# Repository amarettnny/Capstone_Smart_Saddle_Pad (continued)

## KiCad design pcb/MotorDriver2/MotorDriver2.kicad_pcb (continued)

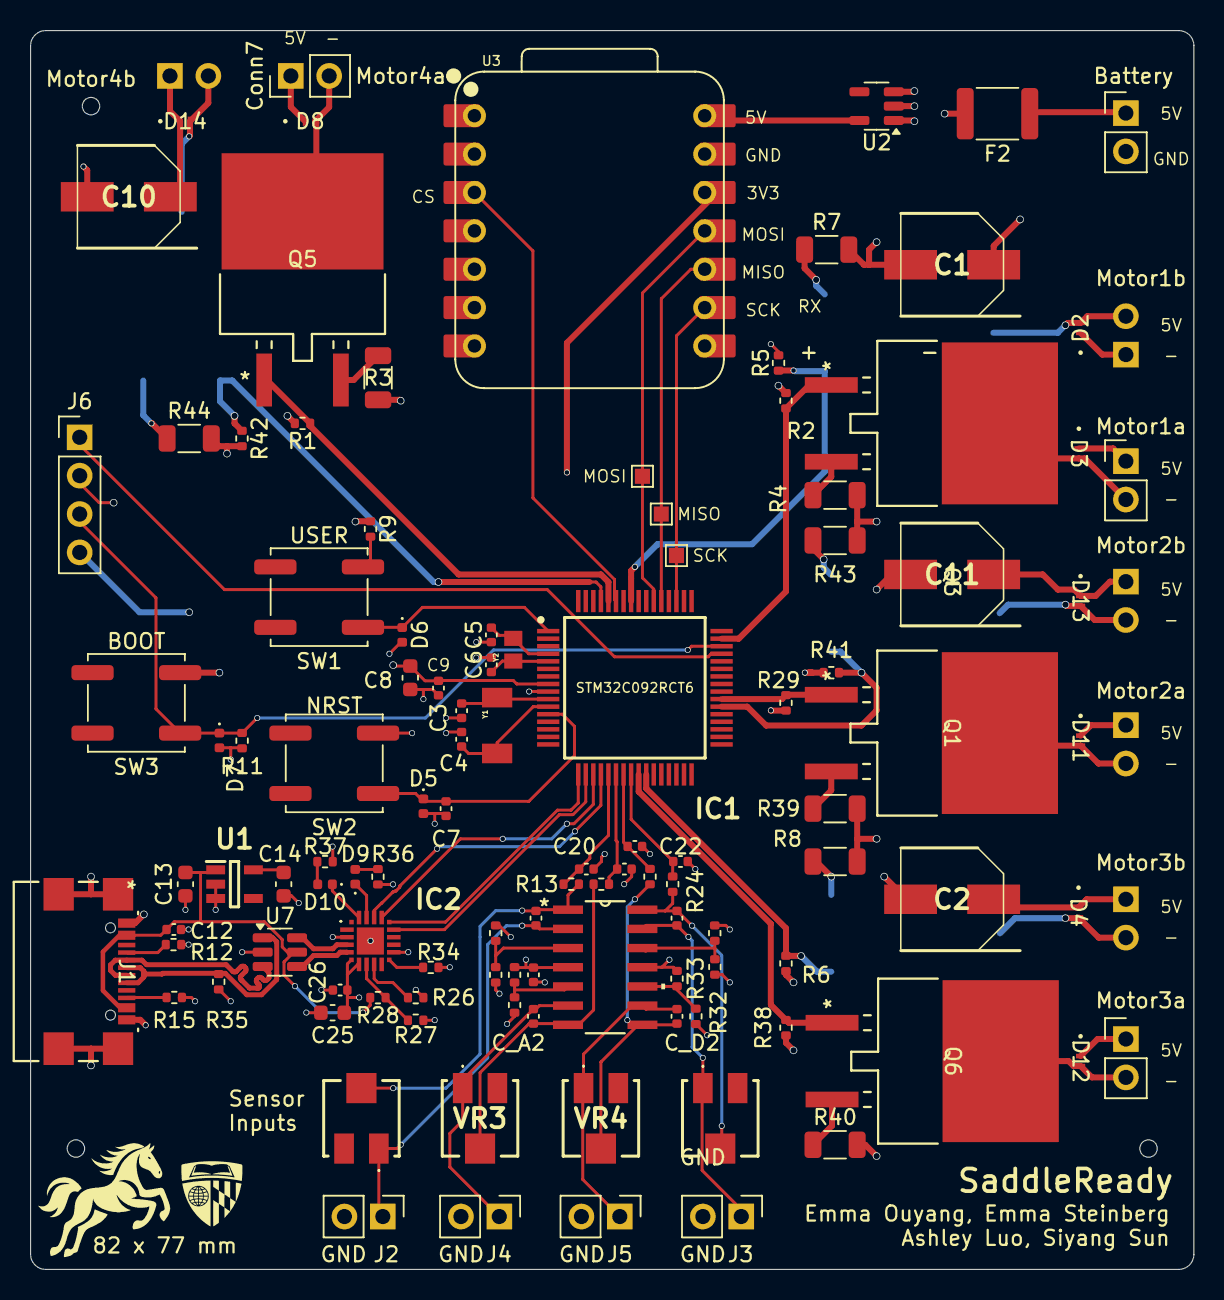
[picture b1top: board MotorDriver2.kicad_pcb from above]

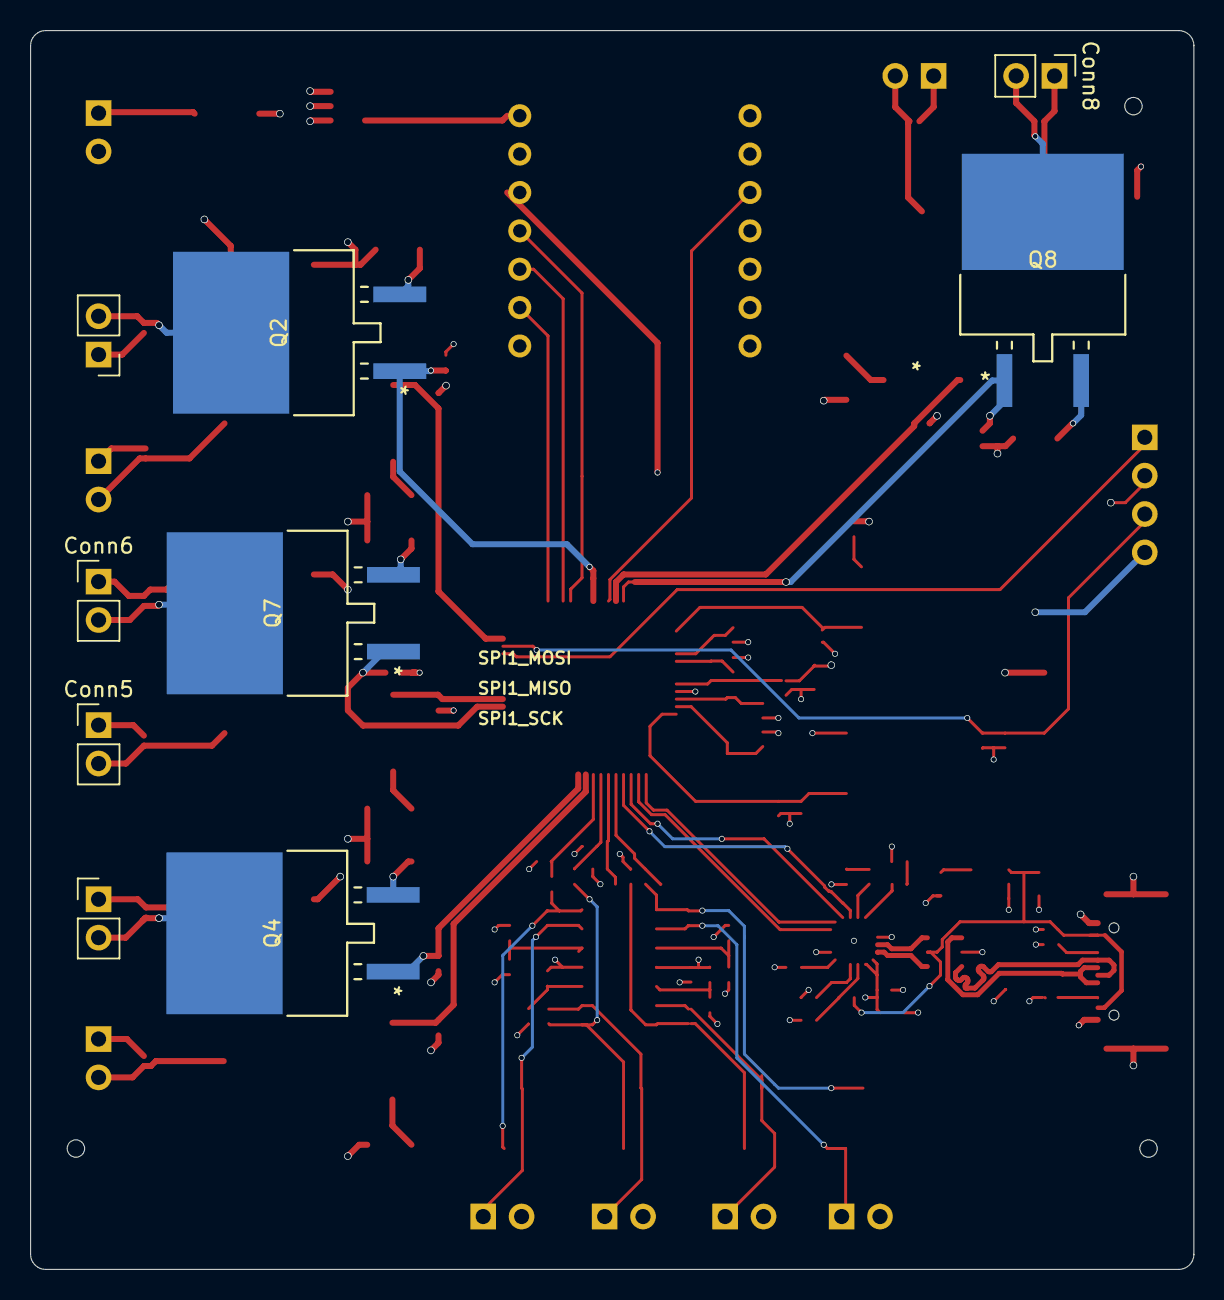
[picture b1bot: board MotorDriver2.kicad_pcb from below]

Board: 4 copper layers, 77.0 x 82.0 mm, 123 parts (9 on the bottom side), 75 nets.

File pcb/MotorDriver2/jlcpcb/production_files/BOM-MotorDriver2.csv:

Comment,Designator,Footprint,LCSC,Quantity
1,"R3,R39,R4,R40,R43,R44,R7,R8",R_1206_3216Metric,C17928,8
1 uF,"C13,C14",C_0603_1608Metric,C15849,2
"1.5k, 1%",R35,R_0402_1005Metric,C25867,1
1.8k,"R18,R19,R31,R33",R_0402_1005Metric,C25871,4
100 nF,"C17,C20,C21,C22,C23,C26,C7,C9",C_0402_1005Metric,C1525,8
100 pF,C12,C_0402_1005Metric,C1546,1
10k,"R1,R11,R16,R17,R2,R29,R30,R32,R34,R38,R41,R42,R5,R6,R9",R_0402_1005Metric,C25744,15
1k,"R26,R36,R37",R_0402_1005Metric,C11702,3
20k,"R13,R14,R24,R25",R_0402_1005Metric,C25765,4
4.7 uF,"C25,C8",C_0603_1608Metric,C19666,2
47 nF,"C_A1,C_A2,C_D1,C_D2",C_0402_1005Metric,C77012,4
"5.1k,10%","R12,R15",R_0402_1005Metric,C25905,2
"7.5 pF, 0.1%","C5,C6",C_0402_1005Metric,C161334,2
"8 pF, 0.1%","C3,C4",C_0402_1005Metric,C3849295,2
CP2102N-A02-GQFN20R,IC2,CP2102NA02GQFN20,C969913,1
ESDALC6V1-1M2,"D5,D6,D7",D_0402_1005Metric,C2649894,3
Honor Elec RVT1H470M0607,"C1,C10,C11,C2",CAPAE680X800N,C3349,4
IRLZ44NSTRLPBF,"Q1,Q2,Q3,Q4,Q5,Q6,Q7,Q8",NMOSGDS_D2PAK_INF,C538199,8
LED,D9,D_0402_1005Metric,C71911,1
LED,D10,D_0402_1005Metric,C74338,1
MAX40200AUK,U2,SOT-23-5,C2649430,1
MINISMDC260F/16-2,F2,Fuse_1812_4532Metric,C16490,1
NCP361SNT1G,U1,SOT95P275X110-5N,C233714,1
SM5819L2-TP,"D11,D12,D13,D14,D2,D3,D4,D8",SDO_SM5819L2-TP_MCE,C6297199,8
STM32C092RCT6,IC1,QFP50P1200X1200X160-64N,C45066876,1
USBLC6-2SC6,U7,SOT-23-6,C7519,1
K2-6639SP-C4SC-04,SW2,K2-6639SP-C4SC-04,,1
Motor2,Conn2,PinHeader_1x02_P2.54mm_Vertical,,1
K2-6639SP-C4SC-04,SW3,K2-6639SP-C4SC-04,,1
Conn_01x02,J2,PinHeader_1x02_P2.54mm_Vertical,,1
32.768 kHz,Y2,MU00527-32.768K,,1
GND,VBAT1,PinHeader_1x02_P2.54mm_Vertical,,1
XIAO-ESP32-C5-DIP,U3,XIAO-ESP32-C5-DIP,,1
48 MHz,Y1,ECS-480-8-30-JGN-TR,,1
Motor4,Conn4,PinHeader_1x02_P2.54mm_Vertical,,1
TS53YJ105MR10,VR2,TS53YJ105MR10,,1
K2-6639SP-C4SC-04,SW1,K2-6639SP-C4SC-04,,1
USB4110-GF-A,J1,USB4110-GF-A_GCT,,1
Conn_01x02,J3,PinHeader_1x02_P2.54mm_Vertical,,1
TS53YJ105MR10,VR1,TS53YJ105MR10,,1
Motor3,Conn3,PinHeader_1x02_P2.54mm_Vertical,,1
Motor1,Conn1,PinHeader_1x02_P2.54mm_Vertical,,1
22.1k,R28,R_0402_1005Metric,,1
TestPoint,TP3,TestPoint_Pad_1.0x1.0mm,,1
TestPoint,TP2,TestPoint_Pad_1.0x1.0mm,,1
TestPoint,TP1,TestPoint_Pad_1.0x1.0mm,,1
Motor8,Conn8,PinHeader_1x02_P2.54mm_Vertical,,1
Motor5,Conn5,PinHeader_1x02_P2.54mm_Vertical,,1
Motor6,Conn6,PinHeader_1x02_P2.54mm_Vertical,,1
Motor7,Conn7,PinHeader_1x02_P2.54mm_Vertical,,1
47.5k,R27,R_0402_1005Metric,,1
LM324DR,U6,D14,,1
Conn_01x02,J4,PinHeader_1x02_P2.54mm_Vertical,,1
Conn_01x02,J5,PinHeader_1x02_P2.54mm_Vertical,,1
TS53YJ105MR10,VR4,TS53YJ105MR10,,1
TS53YJ105MR10,VR3,TS53YJ105MR10,,1
Conn_01x04,J6,PinHeader_1x04_P2.54mm_Vertical,,1

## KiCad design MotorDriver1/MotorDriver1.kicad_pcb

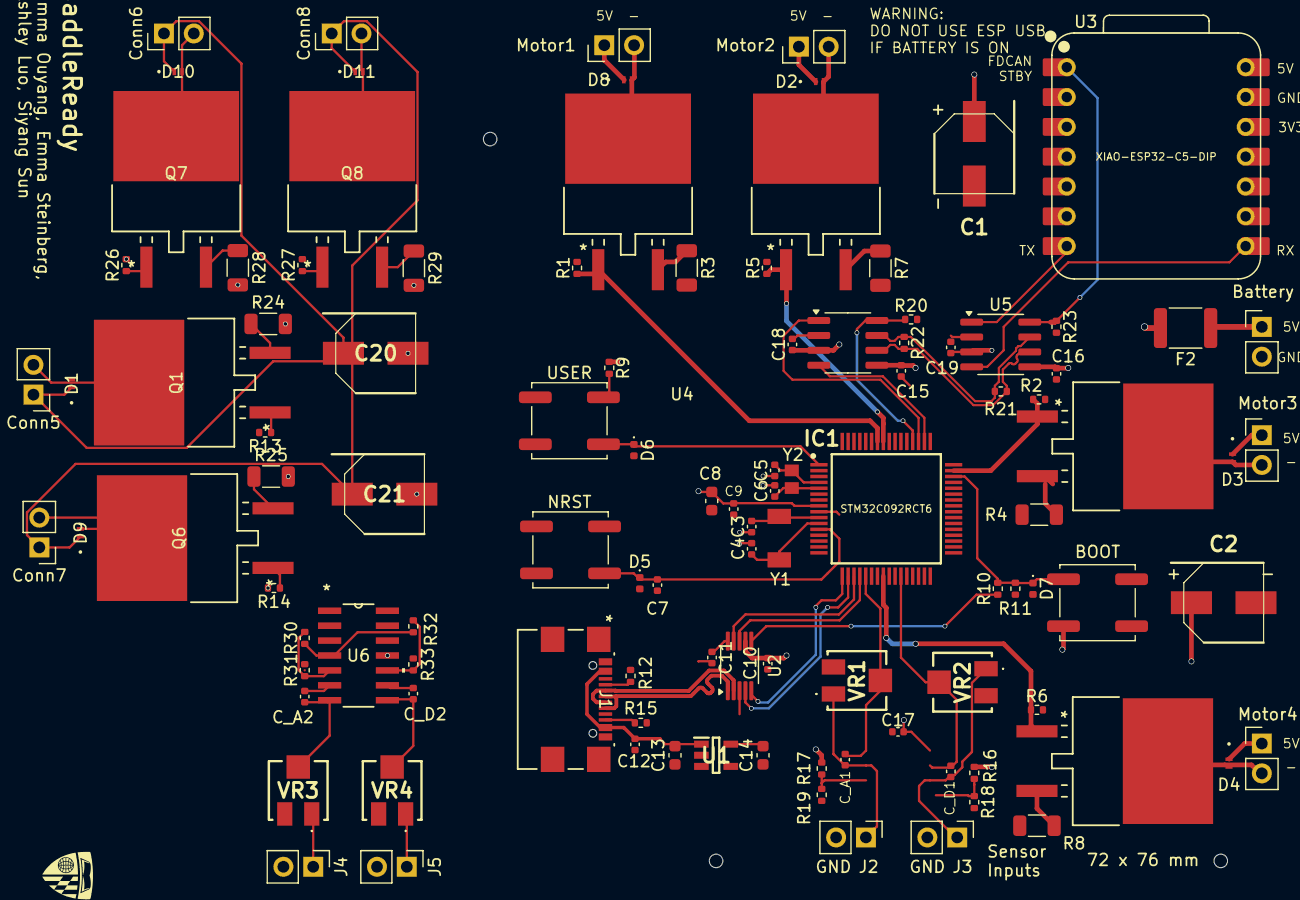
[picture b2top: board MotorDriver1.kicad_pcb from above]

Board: 4 copper layers, 111 parts (0 on the bottom side), 64 nets.

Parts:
C1, C2, C20, C21: MAL214297108E3; CAPAE680X800N
C3, C4: 8 pF, 0.1%; C_0402_1005Metric
C5, C6: 7.5 pF, 0.1%; C_0402_1005Metric
C7, C9, C10, C12, C15, C16, C17, C18, C19: 100 nF; C_0402_1005Metric
C8: 4.7 uF; C_0603_1608Metric
C11: 10 nF; C_0402_1005Metric
C13, C14: 1 uF; C_0603_1608Metric
C_A1, C_A2: 47 nF; C_0402_1005Metric
C_D1, C_D2: 47 nF; C_0402_1005Metric
Conn1: Motor1; PinHeader_1x02_P2.54mm_Vertical
Conn2: Motor2; PinHeader_1x02_P2.54mm_Vertical
Conn3: Motor3; PinHeader_1x02_P2.54mm_Vertical
Conn4: Motor4; PinHeader_1x02_P2.54mm_Vertical
Conn5: Motor5; PinHeader_1x02_P2.54mm_Vertical
Conn6: Motor6; PinHeader_1x02_P2.54mm_Vertical
Conn7: Motor7; PinHeader_1x02_P2.54mm_Vertical
Conn8: Motor8; PinHeader_1x02_P2.54mm_Vertical
D1, D2, D3, D4, D8, D9, D10, D11: SM5819L2-TP; SDO_SM5819L2-TP_MCE
D5, D6, D7: ESDALC6V1-1M2; D_0402_1005Metric
F2: MINISMDC260F/16-2; Fuse_1812_4532Metric
H1, H2, H3: MountingHole; ToolingHole_1.152mm
IC1: STM32C092RCT6; QFP50P1200X1200X160-64N
J1: GT-USB-7010ASV; USB4110-GF-A_GCT
J2, J3, J4, J5: Conn_01x02; PinHeader_1x02_P2.54mm_Vertical
Q1, Q2, Q3, Q4, Q5, Q6, Q7, Q8: IRLZ44NSTRLPBF; NMOSGDS_D2PAK_INF
R1, R2, R5, R6, R9, R11, R13, R14, R16, R17, R20, R23, R26, R27, R30, R32: 10k; R_0402_1005Metric
R3, R4, R7, R8, R24, R25, R28, R29: 1; R_1206_3216Metric
R10: DNP; R_0402_1005Metric
R12, R15: 5.1k,10%; R_0402_1005Metric
R18, R19, R31, R33: 1.8k; R_0402_1005Metric
R21, R22: 120; R_0402_1005Metric
SW1, SW2, SW3: K2-6639SP-C4SC-04
U1: NCP361SNT1G; SOT95P275X110-5N
U2: CH340X; MSOP-10_3x3mm_P0.5mm
U3: XIAO-ESP32-C5-DIP
U4, U5: MCP2562FDT-H/SN; SOIC-8_3.9x4.9mm_P1.27mm
U6: LM324DR; D14
VBAT1: GND; PinHeader_1x02_P2.54mm_Vertical
VR1, VR2, VR3, VR4: TS53YJ105MR10
Y1: 48 MHz; ECS-480-8-30-JGN-TR
Y2: 32.768 kHz; MU00527-32.768K

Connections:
3V3: C8.2, C9.1, C10.2, C15.1, C16.1, C17.1, IC1.8 (VDD/VDDA), R9.1, R16.1, R17.1, R30.1, R32.1, SW3.2, U2.7 (VCC), U3.12 (3V3), U4.5 (Vio), U5.5 (Vio), U6.4 (VCC)
5V: C1.1 (+), C2.1 (+), C18.1, C19.1, C20.1 (+), C21.1 (+), Conn1.1, Conn2.1, Conn3.1, Conn4.1, Conn5.1, Conn6.1, Conn7.1, Conn8.1, D1.1 (K), D2.1 (K), D3.1 (K), D4.1 (K), D8.1 (K), D9.1 (K), D10.1 (K), D11.1 (K), F2.2, U3.14 (VBUS), U4.3 (VDD), U5.3 (VDD)
5V_USB: C14.2, U1.5 (OUT)
!CTS: IC1.17 (PA0), U2.5 (~CTS)
!DTR: R10.1, U2.6 (TNOW/~DTR)
!RTS: IC1.18 (PA1), U2.4 (~RTS)
/FDCAN/CAN_N: R21.2, R22.2, U4.6 (CANL), U5.6 (CANL)
/FDCAN/CAN_P: R21.1, R22.1, U4.7 (CANH), U5.7 (CANH)
/motorDriver_Pads12/Motor1-: Conn1.2, D8.2 (A), Q5.2 (D)
/motorDriver_Pads12/Motor2-: Conn2.2, D2.2 (A), Q2.2 (D)
/motorDriver_Pads12/Motor3-: Conn3.2, D3.2 (A), Q3.2 (D)
/motorDriver_Pads12/Motor4-: Conn4.2, D4.2 (A), Q4.2 (D)
/motorDriver_Pads34/Motor5-: Conn5.2, D1.2 (A), Q1.2 (D)
/motorDriver_Pads34/Motor6-: Conn6.2, D10.2 (A), Q7.2 (D)
/motorDriver_Pads34/Motor7-: Conn7.2, D9.2 (A), Q6.2 (D)
/motorDriver_Pads34/Motor8-: Conn8.2, D11.2 (A), Q8.2 (D)
/stm32/PC14: C5.2, IC1.4 (PC14-OSCX_IN), Y2.2
/stm32/PC15: C6.1, IC1.5 (PC15-OSCX_OUT), Y2.1
/stm32/PF0: C3.2, IC1.10 (PF0-OSC_IN), Y1.2
/stm32/PF1: C4.1, IC1.11 (PF1-OSC_OUT), Y1.1
BOOT: D7.1 (K), IC1.46 (PA14-BOOT0), R10.2, R11.1, SW3.4
FDCAN_RX_ESP: U3.8 (GPIO20_D7_RX), U5.4 (RXD)
FDCAN_RX_STM: IC1.50 (PD0), U4.4 (RXD)
FDCAN_STBY_ESP: R23.1, U3.1 (GPIO2_A0_D0), U5.8 (STBY)
FDCAN_STBY_STM: IC1.52 (PD2), R20.1, U4.8 (STBY)
FDCAN_TX_ESP: U3.7 (GPIO21_D6_TX), U5.1 (TXD)
FDCAN_TX_STM: IC1.51 (PD1), U4.1 (TXD)
GND: C1.2 (-), C2.2 (-), C3.1, C4.2, C5.1, C6.2, C7.2, C8.1, C9.2, C10.1, C11.2, C12.1, C13.1, C14.1, C15.2, C16.2, C17.2, C18.2, C19.2, C20.2 (-), C21.2 (-), D5.2 (A), D6.2 (A), D7.2 (A), IC1.9 (VSS/VSSA), J1.15 (GND), J1.16 (GND), J1.17 (GND), J1.18 (GND), J1.A1-B12 (GND), J1.A12-B1 (GND), J2.2, J3.2, J4.2, J5.2, R1.2, R2.2, R3.2, R4.2, R5.2, R6.2, R7.2, R8.2, R11.2, R12.1, R13.2, R14.2, R15.1, R18.2, R19.2, R20.2, R23.2, R24.2, R25.2, R26.2, R27.2, R28.2, R29.2, R31.2, R33.2, SW2.2, U1.2 (GND), U1.3 (~EN), U2.3 (GND), U3.13 (GND), U4.2 (VSS), U5.2 (VSS), U6.11 (GND), VBAT1.2
Motor1_PWM: IC1.58 (PB4), Q1.1 (G), Q5.1 (G), R1.1, R13.1
Motor2_PWM: IC1.57 (PB3), Q2.1 (G), Q7.1 (G), R5.1, R26.1
Motor3_PWM: IC1.47 (PA15), Q3.1 (G), Q6.1 (G), R2.1, R14.1
Motor4_PWM: IC1.24 (PA7), Q4.1 (G), Q8.1 (G), R6.1, R27.1
NRST: C7.1, D5.1 (K), IC1.12 (PF2-NRST), SW2.4
unnamed: J1.A5 (CC1), R12.2
unnamed: J1.B5 (CC2), R15.2
unnamed: Q1.3 (S), R24.1
unnamed: Q5.3 (S), R3.1
unnamed: Q2.3 (S), R7.1
unnamed: Q3.3 (S), R4.1
unnamed: Q4.3 (S), R8.1
unnamed: Q6.3 (S), R25.1
unnamed: Q7.3 (S), R28.1
unnamed: Q8.3 (S), R29.1
unnamed: R9.2, SW1.2
unnamed: C11.1, U2.10 (V3)
unnamed: F2.1, VBAT1.1
SensorAIn: C_A1.2, J2.1, U6.2 (1IN-), VR1.A1 (CCW)
SensorAOut: C_A1.1, IC1.21 (PA4), U6.1 (1OUT), VR1.B1 (WIPER)
SensorA_0.5V: R17.2, R19.1, U6.3 (1IN+)
SensorBIn: C_A2.2, J4.1, U6.6 (2IN-), VR3.A1 (CCW)
SensorBOut: C_A2.1, U6.7 (2OUT), VR3.B1 (WIPER)
SensorB_0.5V: R30.2, R31.1, U6.5 (2IN+)
SensorCIn: C_D2.1, J5.1, U6.9 (3IN-), VR4.A1 (CCW)
SensorCOut: C_D2.2, U6.8 (3OUT), VR4.B1 (WIPER)
SensorC_0.5V: R32.2, R33.1, U6.10 (3IN+)
SensorDIn: C_D1.1, J3.1, U6.13 (4IN-), VR2.A1 (CCW)
SensorDOut: C_D1.2, IC1.27 (PB0), U6.14 (4OUT), VR2.B1 (WIPER)
SensorD_0.5V: R16.2, R18.1, U6.12 (4IN+)
USART2_RX: IC1.20 (PA3), U2.8 (TXD)
USART2_TX: IC1.19 (PA2), U2.9 (RXD)
USB_D+: J1.A6 (DP1), J1.B6 (DP2), U2.1 (UD+)
USB_D-: J1.A7 (DN1), J1.B7 (DN2), U2.2 (UD-)
USER_BTN: D6.1 (K), IC1.1 (PC11), SW1.4
VBUS: C12.2, C13.2, J1.A4-B9 (VBUS), J1.A9-B4 (VBUS), U1.1 (IN)

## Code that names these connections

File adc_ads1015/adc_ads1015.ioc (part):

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Mcu.Name=STM32C092RCTx
Mcu.Package=LQFP64
Mcu.UserName=STM32C092RCTx
PA13.GPIOParameters=GPIO_Label
PA13.GPIO_Label=SWDIO
PA13.Signal=DEBUG_SWDIO
PA14-BOOT0.GPIOParameters=GPIO_Label
PA14-BOOT0.GPIO_Label=SWCLK
PA14-BOOT0.Signal=DEBUG_SWCLK
PA2.GPIOParameters=GPIO_Label
PA2.GPIO_Label=VCP_TX
PA2.Mode=Asynchronous
PA2.Signal=USART2_TX
PA3.GPIOParameters=GPIO_Label
PA3.GPIO_Label=VCP_RX
PA3.Mode=Asynchronous
PA3.Signal=USART2_RX
PA5.GPIOParameters=GPIO_Label
PA5.GPIO_Label=User LED1
PA5.Signal=GPIO_Output
PA6.Mode=I2C
PA6.Signal=I2C2_SDA
PA7.Mode=I2C
PA7.Signal=I2C2_SCL
PC13.GPIOParameters=GPIO_Label
PC13.GPIO_Label=User button
PC13.Signal=GPIO_Input
PC14-OSCX_IN(PC14).GPIOParameters=GPIO_Label
PC14-OSCX_IN(PC14).GPIO_Label=OSCX_IN
PC14-OSCX_IN(PC14).Signal=RCC_OSCX_IN
PC15-OSCX_OUT(PC15).GPIOParameters=GPIO_Label
PC15-OSCX_OUT(PC15).GPIO_Label=OSCX_OUT
PC15-OSCX_OUT(PC15).Signal=RCC_OSCX_OUT
PF0-OSC_IN(PF0).GPIOParameters=GPIO_Label
PF0-OSC_IN(PF0).GPIO_Label=OSC_IN
PF0-OSC_IN(PF0).Signal=RCC_OSC_IN
PF1-OSC_OUT(PF1).GPIOParameters=GPIO_Label
PF1-OSC_OUT(PF1).GPIO_Label=OSC_OUT
PF1-OSC_OUT(PF1).Signal=RCC_OSC_OUT
RCC.HSE_VALUE=8000000
RCC.SYSCLKFreq_VALUE=12000000
board=NUCLEO-C092RC
boardIOC=true

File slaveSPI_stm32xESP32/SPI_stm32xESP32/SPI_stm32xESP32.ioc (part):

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Mcu.Name=STM32C092RCTx
Mcu.Package=LQFP64
Mcu.UserName=STM32C092RCTx
PA2.Mode=Asynchronous
PA2.Signal=USART2_TX
PA3.Mode=Asynchronous
PA3.Signal=USART2_RX
PA5.Mode=Full_Duplex_Slave
PA5.Signal=SPI1_SCK
PA6.Mode=Full_Duplex_Slave
PA6.Signal=SPI1_MISO
PA7.Mode=Full_Duplex_Slave
PA7.Signal=SPI1_MOSI
PC13.Signal=GPIO_Input
PD0.Signal=FDCAN1_RX
PD1.Signal=FDCAN1_TX
PF0-OSC_IN(PF0).Mode=HSE-External-Oscillator
PF0-OSC_IN(PF0).Signal=RCC_OSC_IN
PF1-OSC_OUT(PF1).Mode=HSE-External-Oscillator
PF1-OSC_OUT(PF1).Signal=RCC_OSC_OUT
RCC.HSE_VALUE=48000000
RCC.SYSCLKFreq_VALUE=48000000
RCC.SYSCLKSource=RCC_SYSCLKSOURCE_HSE
board=custom

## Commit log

2026-01-29 Created new branch
2026-01-29 Update README.md with ESP-IDF instructions
2026-01-29 Setting up esp-idf (missing .vscode directory
2026-01-29 Finished setting up esp-idf with VSCode
2026-02-05 Wrote initial BLE code
2026-03-02 Latest updates
2026-03-02 Created gitignore file
2026-03-02 Created PCB schematic
2026-03-02 added dummy files to empty footprint and symbol folders
2026-03-02 Set up KiCad libraries & STM32 page
2026-03-03 Edited STM32 schematic
2026-03-03 Added net labels and global lables to motor driver
2026-03-08 added pressure sensor and flags to STM need op amp rails
2026-03-08 added op amp rails
2026-03-08 input output flags for sensor signals
2026-03-09 updated motor and sensor schematics and added footprints
2026-03-12 missing crystal verification
2026-03-12 Updated footprints
2026-03-12 assigned eo footprints
2026-03-12 laid out PCB
2026-03-12 modifications to PCB layout
2026-03-12 Re-layed out eo stuff
2026-03-12 component placing and first traces
2026-03-12 Created new crystal footprints
2026-03-12 Updated crystal footprints
2026-03-12 new BOM
2026-03-13 Exported final JLCPCB files
2026-03-13 Tuned skew
2026-03-13 Added tooling holes
2026-03-13 Re-did parts of bom
2026-03-13 Re-generated gerbers
2026-03-13 Added battery fuse
2026-04-02 Using ESP32 twai_self_test
2026-04-06 Built and tested on ESP32S3, had build issues on ESP32C5
2026-04-09 added motors and sensors for 4 pad system
2026-04-09 Tested TWAI examples
2026-04-09 Re-organized pcb files
2026-04-09 Modifying usb uart schematic
2026-04-10 Modified pwm pins
2026-04-10 added ideal diode protection
2026-04-11 Laying out PCB
2026-04-11 Finished pcb layout
2026-04-13 Added STLink Connector
2026-04-13 Removed can transceivers, replaced with spi
2026-04-27 Pushed SPI code
2026-04-27 adc reading 4 channels
2026-04-28 Made some edits while making design poster
2026-04-28 Added step files
